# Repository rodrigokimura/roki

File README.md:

# RoKi

> An ergonomic, wireless, split mechanical keyboard — hardware, firmware and tooling in one repo.

**RoKi** (from the author's surname) is a custom, from-scratch split keyboard project. It covers the full stack: PCB design, 3D-printable case parts, CircuitPython firmware running on the [nice!nano v2](https://nicekeyboards.com/docs/nice-nano/) (wireless Bluetooth Low Energy controller), and a companion Python CLI / web UI / TUI to flash, configure and debug the board.

> ⚠️ **Status:** Work in progress. Breaking changes are expected.

---

## Features

- **Split layout** with BLE-based inter-half communication (no TRRS cable).
- **5 rows × 6 columns** per half, diode matrix.
- **Thumb cluster with analog thumbstick** (for pointer / scroll / layer control).
- **Rotary encoder** on each half.
- **Piezo buzzer** for audio feedback.
- **Layer system** with custom `layer_handler` (tap / hold / toggle commands).
- **HID support** for keyboard, mouse and consumer-control (media) keys, via `adafruit_hid`.
- **Per-side configuration** (primary / secondary) selected via environment.
- **Runtime calibration** of the analog thumbstick (deadzone, center, range).
- **Read-only filesystem toggle** at boot, driven by a hardware switch, so you can
  hot-swap between "keyboard mode" and "developer mode" without rebuilding firmware.

---

## Repository layout

```
roki/
├── roki/                    # Python package
│   ├── firmware/            # CircuitPython firmware (runs on nice!nano v2)
│   │   ├── boot.py          # Early boot: filesystem readonly switch
│   │   ├── code.py          # Main entry point, pin mapping
│   │   ├── kb.py            # Primary / Secondary keyboard classes
│   │   ├── keys.py          # HID key definitions and handlers
│   │   ├── layer_handler.py # Layer / Command system
│   │   ├── calibration.py   # Thumbstick calibration
│   │   ├── config.py        # Runtime config model + JSON loader
│   │   ├── service.py       # BLE service for half-to-half comms
│   │   ├── buzzer.py        # Audio feedback
│   │   ├── logging.py       # Color-coded adafruit_logging formatter
│   │   ├── params.py        # Env-based parameter singleton
│   │   └── config.json      # Default key map / layers
│   ├── cli/                 # Host-side CLI (typer)
│   │   ├── app.py           # `roki` command entry point
│   │   ├── utils.py         # Mount / unmount / lib install helpers
│   │   ├── file_management.py
│   │   ├── html_generator.py
│   │   └── logging.py
│   ├── tui/                 # Textual-based TUI key-map configurator
│   │   ├── app.py
│   │   ├── screens/
│   │   └── widgets/
│   └── templates/           # HTML templates for the web UI
├── tests/                   # pytest suite (firmware + cli)
├── kicad/roki/              # PCB design (schematic, layout, 3D step)
├── freecad/                 # Case, keycaps, thumbstick, encoder, etc.
├── conftest.py              # Global mocks for CircuitPython modules
└── pyproject.toml
```

---

## Hardware

| Item                | Choice                                        |
|---------------------|-----------------------------------------------|
| Microcontroller     | [nice!nano v2](https://nicekeyboards.com/docs/nice-nano/pinout-schematic/) (nRF52840, BLE) |
| Layout              | Split, 5×6 + thumb cluster + encoder per half |
| Switches            | MX-compatible, hotswap                        |
| Inter-half comms    | Bluetooth Low Energy (custom GATT service)    |
| Power               | Li-Po, per-half power switch                  |
| Analog input        | Thumbstick (X / Y + push)                     |

PCB sources live in [`kicad/roki/`](./kicad/roki/). Case, keycaps and mechanical parts live in [`freecad/`](./freecad/) as `.FCStd` files.

---

## Firmware (CircuitPython)

Runs on CircuitPython for nRF52840. The firmware is structured around a `Primary` / `Secondary` pair of keyboard halves:

- **Primary** holds the full config, scans its own matrix, talks HID over BLE to the host, and receives key events from the secondary over a custom BLE service.
- **Secondary** scans its matrix and forwards events to the primary.

The side is chosen at boot via the `IS_LEFT_SIDE` environment variable (or the `boot.py` switch pin), so the same code runs on both halves.

### Pin mapping

Defined in [`roki/firmware/code.py`](./roki/firmware/code.py):

```python
Roki(
    row_pins=("P0_24", "P1_00", "P0_11", "P1_04", "P1_06"),
    column_pins=("P0_09", "P0_10", "P1_11", "P1_13", "P1_15", "P0_02"),
    buzzer_pin="P0_06",
    thumb_stick_pins=("P0_22", "AIN7", "AIN5"),  # switch, X, Y
    encoder_pins=("P0_17", "P0_20"),
)
```

See the [nice!nano pinout & schematic](https://nicekeyboards.com/docs/nice-nano/pinout-schematic/) for reference.

### Boot-time write protection

`boot.py` reads pin `P0_22` on startup. When the switch is **open** the filesystem is mounted read-only (normal keyboard mode); when **closed**, read-write — useful for editing files over USB without your OS fighting CircuitPython.

---

## Host-side tooling

A `typer` CLI is installed as `roki`:

```sh
roki upload        # (alias: u)  Flash firmware + libs to the connected board
roki run           #             Launch the TUI key-map configurator
roki serve         #             Start the FastAPI + Jinja web config UI
roki generate      # (alias: g)  Generate static HTML / artifacts
roki config        #             Show / edit config.json
```

### Install

```sh
uv sync
```

(Uses [uv](https://docs.astral.sh/uv/) as the package manager; Python 3.12+.)

### Run the tests

```sh
uv run pytest
```

With coverage:

```sh
uv run pytest --cov=roki --cov-report=term
```

Current coverage: **88%** across ~2.3k lines of source with 109 tests.

### Run the web configurator locally (HTTPS)

```sh
# Generate self-signed certs once
openssl req -x509 -newkey rsa:2048 -keyout key.pem -out cert.pem -days 365

uv run roki serve
```

---

## Environment variables

Set in `roki/firmware/settings.toml` on the board, or via your shell for host-side runs:

| Variable        | Default | Meaning                                     |
|-----------------|---------|---------------------------------------------|
| `IS_LEFT_SIDE`  | `1`     | `1` for primary (left), `0` for secondary   |
| `DEBUG`         | `0`     | `1` enables the stream logger               |
| `LOG_LEVEL`     | `0`     | Standard logging levels (10 = DEBUG, etc.)  |

---

## Development workflow

This repo uses [commitizen](https://commitizen-tools.github.io/commitizen/) for [Conventional Commits](https://www.conventionalcommits.org/) and [ruff](https://docs.astral.sh/ruff/) for linting / import sorting.

```sh
uv run cz commit            # interactive commit
uv run ruff check --fix .   # lint + autofix
uv run ruff format .        # format
```

Pre-commit hooks are configured in [`.pre-commit-config.yaml`](./.pre-commit-config.yaml).

---

## License

[MIT](./LICENSE) © Rodrigo Eiti Kimura

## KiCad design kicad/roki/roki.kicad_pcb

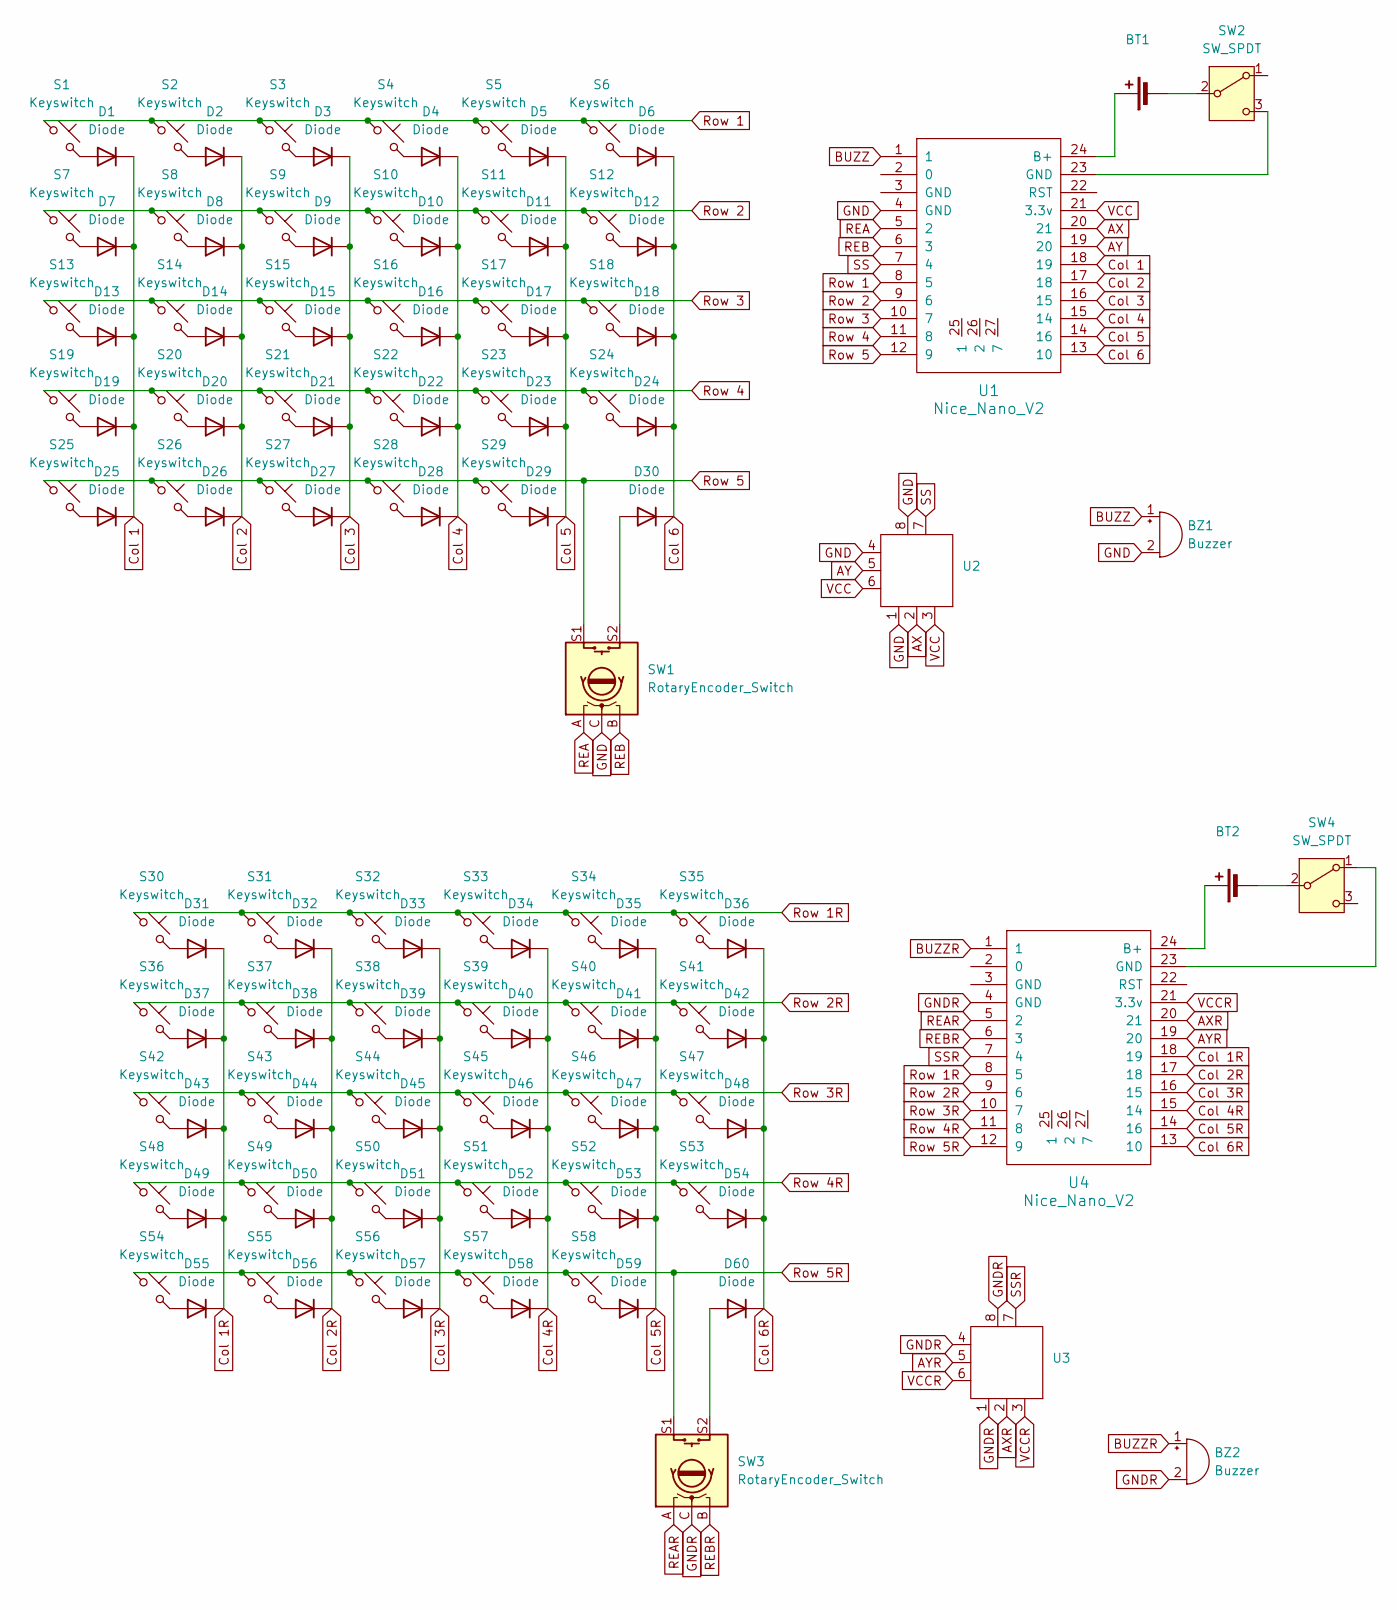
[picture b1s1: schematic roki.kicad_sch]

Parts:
BT1, BT2: Battery_Cell; BatteryHolder_MPD_BH-18650-PC2
BZ1, BZ2: Buzzer; Buzzer_TDK_PS1240P02BT_D12.2mm_H6.5mm
D1, D2, D3, D4, D5, D6, D7, D8, D9, D10, D11, D12, D13, D14, D15, D16, D17, D18, D19, D20, D21, D22, D23, D24, D25, D26, D27, D28, D29, D30, D31, D32, D33, D34, D35, D36, D37, D38, D39, D40, D41, D42, D43, D44, D45, D46, D47, D48, D49, D50, D51, D52, D53, D54, D55, D56, D57, D58, D59, D60: Diode; Diode_SOD-123
S1, S2, S3, S4, S5, S6, S7, S8, S9, S10, S11, S12, S13, S14, S15, S16, S17, S18, S19, S20, S21, S22, S23, S24, S25, S26, S27, S28, S29, S30, S31, S32, S33, S34, S35, S36, S37, S38, S39, S40, S41, S42, S43, S44, S45, S46, S47, S48, S49, S50, S51, S52, S53, S54, S55, S56, S57, S58: Keyswitch; Hotswap_MX_1.00u
SW1, SW3: RotaryEncoder_Switch; RotaryEncoder_Alps_EC11E-Switch_Vertical_H20mm
SW2, SW4: SW_SPDT; SW_SPDT_PCM12
U1, U4: Nice_Nano_V2
U2, U3: thumb_stick

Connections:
AX: U1.20 (21), U2.2
AXR: U3.2, U4.20 (21)
AY: U1.19 (20), U2.5
AYR: U3.5, U4.19 (20)
BUZZ: BZ1.1 (+), U1.1
BUZZR: BZ2.1 (+), U4.1
Col 1: D1.1 (K), D7.1 (K), D13.1 (K), D19.1 (K), D25.1 (K), U1.18 (19)
Col 1R: D31.1 (K), D37.1 (K), D43.1 (K), D49.1 (K), D55.1 (K), U4.18 (19)
Col 2: D2.1 (K), D8.1 (K), D14.1 (K), D20.1 (K), D26.1 (K), U1.17 (18)
Col 2R: D32.1 (K), D38.1 (K), D44.1 (K), D50.1 (K), D56.1 (K), U4.17 (18)
Col 3: D3.1 (K), D9.1 (K), D15.1 (K), D21.1 (K), D27.1 (K), U1.16 (15)
Col 3R: D33.1 (K), D39.1 (K), D45.1 (K), D51.1 (K), D57.1 (K), U4.16 (15)
Col 4: D4.1 (K), D10.1 (K), D16.1 (K), D22.1 (K), D28.1 (K), U1.15 (14)
Col 4R: D34.1 (K), D40.1 (K), D46.1 (K), D52.1 (K), D58.1 (K), U4.15 (14)
Col 5: D5.1 (K), D11.1 (K), D17.1 (K), D23.1 (K), D29.1 (K), U1.14 (16)
Col 5R: D35.1 (K), D41.1 (K), D47.1 (K), D53.1 (K), D59.1 (K), U4.14 (16)
Col 6: D6.1 (K), D12.1 (K), D18.1 (K), D24.1 (K), D30.1 (K), U1.13 (10)
Col 6R: D36.1 (K), D42.1 (K), D48.1 (K), D54.1 (K), D60.1 (K), U4.13 (10)
GND: BZ1.2 (-), SW1.C, U1.4 (GND), U2.1, U2.4, U2.8
GNDR: BZ2.2 (-), SW3.C, U3.1, U3.4, U3.8, U4.4 (GND)
unnamed: BT1.1 (+), U1.24 (B+)
unnamed: BT1.2 (-), SW2.2 (B)
unnamed: BT2.1 (+), U4.24 (B+)
unnamed: BT2.2 (-), SW4.2 (B)
unnamed: D1.2 (A), S1.2
unnamed: D2.2 (A), S2.2
unnamed: D3.2 (A), S3.2
unnamed: D4.2 (A), S4.2
unnamed: D5.2 (A), S5.2
unnamed: D6.2 (A), S6.2
unnamed: D7.2 (A), S7.2
unnamed: D8.2 (A), S8.2
unnamed: D9.2 (A), S9.2
unnamed: D10.2 (A), S10.2
unnamed: D11.2 (A), S11.2
unnamed: D12.2 (A), S12.2
unnamed: D13.2 (A), S13.2
unnamed: D14.2 (A), S14.2
unnamed: D15.2 (A), S15.2
unnamed: D16.2 (A), S16.2
unnamed: D17.2 (A), S17.2
unnamed: D18.2 (A), S18.2
unnamed: D19.2 (A), S19.2
unnamed: D20.2 (A), S20.2
unnamed: D21.2 (A), S21.2
unnamed: D22.2 (A), S22.2
unnamed: D23.2 (A), S23.2
unnamed: D24.2 (A), S24.2
unnamed: D25.2 (A), S25.2
unnamed: D26.2 (A), S26.2
unnamed: D27.2 (A), S27.2
unnamed: D28.2 (A), S28.2
unnamed: D29.2 (A), S29.2
unnamed: D30.2 (A), SW1.S2
unnamed: D31.2 (A), S30.2
unnamed: D32.2 (A), S31.2
unnamed: D33.2 (A), S32.2
unnamed: D34.2 (A), S33.2
unnamed: D35.2 (A), S34.2
unnamed: D36.2 (A), S35.2
unnamed: D37.2 (A), S36.2
unnamed: D38.2 (A), S37.2
unnamed: D39.2 (A), S38.2
unnamed: D40.2 (A), S39.2
unnamed: D41.2 (A), S40.2
unnamed: D42.2 (A), S41.2
unnamed: D43.2 (A), S42.2
unnamed: D44.2 (A), S43.2
unnamed: D45.2 (A), S44.2
unnamed: D46.2 (A), S45.2
unnamed: D47.2 (A), S46.2
unnamed: D48.2 (A), S47.2
unnamed: D49.2 (A), S48.2
unnamed: D50.2 (A), S49.2
unnamed: D51.2 (A), S50.2
unnamed: D52.2 (A), S51.2
unnamed: D53.2 (A), S52.2
unnamed: D54.2 (A), S53.2
unnamed: D55.2 (A), S54.2
unnamed: D56.2 (A), S55.2
unnamed: D57.2 (A), S56.2
unnamed: D58.2 (A), S57.2
unnamed: D59.2 (A), S58.2
unnamed: D60.2 (A), SW3.S2
unnamed: SW2.3 (C), U1.23 (GND)
unnamed: SW4.1 (A), U4.23 (GND)
REA: SW1.A, U1.5 (2)
REAR: SW3.A, U4.5 (2)
REB: SW1.B, U1.6 (3)
REBR: SW3.B, U4.6 (3)
Row 1: S1.1, S2.1, S3.1, S4.1, S5.1, S6.1, U1.8 (5)
Row 1R: S30.1, S31.1, S32.1, S33.1, S34.1, S35.1, U4.8 (5)
Row 2: S7.1, S8.1, S9.1, S10.1, S11.1, S12.1, U1.9 (6)
Row 2R: S36.1, S37.1, S38.1, S39.1, S40.1, S41.1, U4.9 (6)
Row 3: S13.1, S14.1, S15.1, S16.1, S17.1, S18.1, U1.10 (7)
Row 3R: S42.1, S43.1, S44.1, S45.1, S46.1, S47.1, U4.10 (7)
Row 4: S19.1, S20.1, S21.1, S22.1, S23.1, S24.1, U1.11 (8)
Row 4R: S48.1, S49.1, S50.1, S51.1, S52.1, S53.1, U4.11 (8)
Row 5: S25.1, S26.1, S27.1, S28.1, S29.1, SW1.S1, U1.12 (9)
Row 5R: S54.1, S55.1, S56.1, S57.1, S58.1, SW3.S1, U4.12 (9)
SS: U1.7 (4), U2.7
SSR: U3.7, U4.7 (4)
VCC: U1.21 (3.3v), U2.3, U2.6
VCCR: U3.3, U3.6, U4.21 (3.3v)

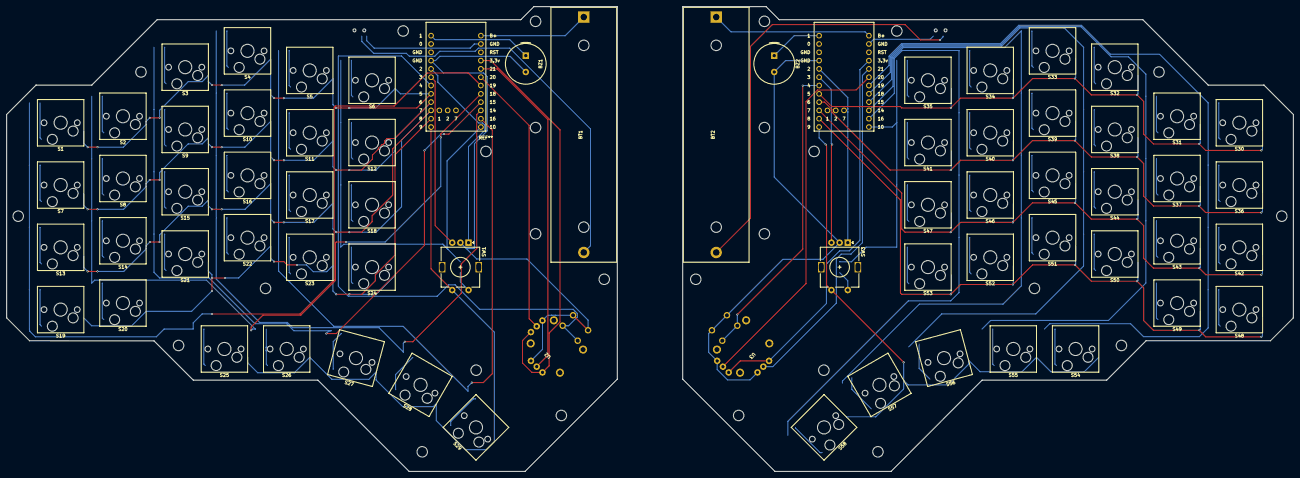
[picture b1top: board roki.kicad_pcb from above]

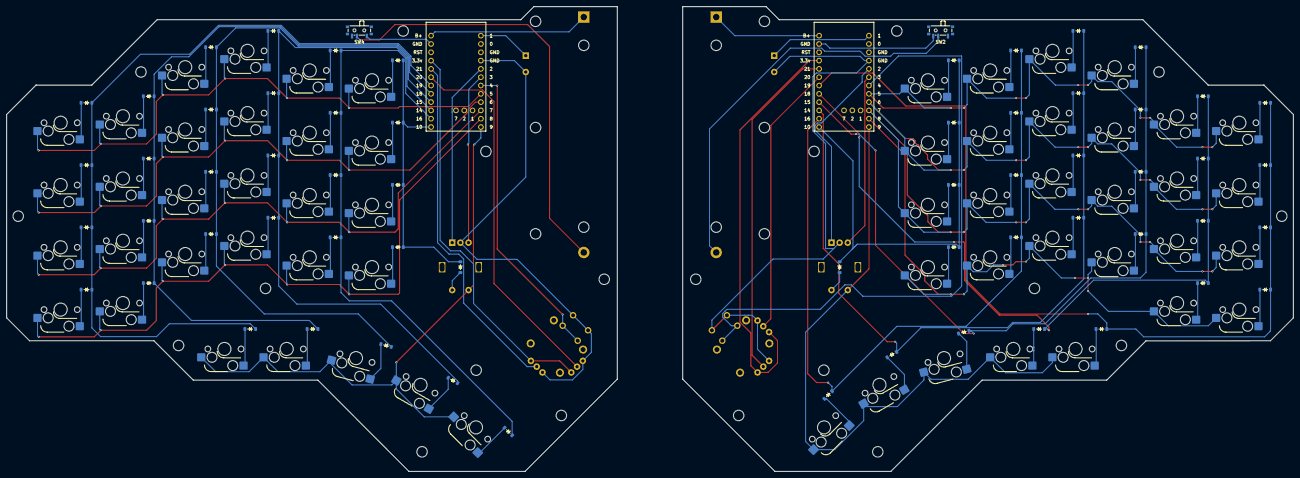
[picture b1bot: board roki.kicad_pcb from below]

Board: 2 copper layers, 393.6 x 142.2 mm, 130 parts (62 on the bottom side), 104 nets.

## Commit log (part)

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2024-09-05 feat: create first working version
2024-09-05 build(deps): update deps
2024-09-12 feat: add file management functions
2024-09-12 refactor(cli): abstract low-level file management logic
2024-09-12 refactor(firmware): remove unused code
2024-09-12 ci: add and configure commitizen
2024-09-12 feat(firmware): use scroll lock as layer state
2024-09-12 fix(firmware): protect against exception
2024-09-17 feat(firmware): add first draft of central-peripheral communication
2024-09-18 feat(firmware): implement packet buffer service
2024-09-18 fix(firmware): reimplement layers using central-peripheral connection
2024-10-09 fix(cli): copy file after its update
2024-10-29 perf(firmware): decrease connection interval
2024-11-05 feat(firmware): add encoder object
2024-11-05 feat(firmware): add main class for the keyboard
2024-11-05 refactor(firmware): use main class
2024-11-05 perf(firmware): cache row and column count
2024-11-09 feat(firmware): add encoder feature
2024-11-09 docs(readme): add pinout and schematic link
2024-11-09 refactor(firmware): simplify methods
2024-11-29 feat(cli): add commands for configuration page
2024-12-02 build(deps): add textual
2024-12-02 fix: remove unused code
2024-12-02 feat(tui): add configurator tui
2024-12-08 feat(firmware): implement new communication protocol
2024-12-08 fix(cli): change options for upload command
2024-12-09 build(poetry): add coverage deps
2024-12-10 feat(firmware): add thumb stick analog inputs
2024-12-10 test: add tests
2024-12-10 feat(firmware): add protocol to send and parse thumb stick data
2024-12-11 fix(tui): fix imports
2024-12-12 feat(firmware): process secondary thumb stick
2024-12-15 feat(kicad): add kicak files
2024-12-15 feat(freecad): add freecad files
2024-12-24 build(deps): bump jinja2 from 3.1.4 to 3.1.5
    Bumps [jinja2](https://github.com/pallets/jinja) from 3.1.4 to 3.1.5.
    - [Release notes](https://github.com/pallets/jinja/releases)
    - [Changelog](https://github.com/pallets/jinja/blob/main/CHANGES.rst)
    - [Commits](https://github.com/pallets/jinja/compare/3.1.4...3.1.5)
    ---
    updated-dependencies:
2024-12-25 feat(firmware): add calibration algorithm
2025-01-08 feat(cli): allow https on local setup
2025-01-09 build(deps): fix dependency tree
2025-01-09 fix(kicad): fix thumb stick pin schematics
2025-01-23 feat(firmware): write calibration data
2025-01-24 feat(firmware): implement thumb stick mid value
2025-01-24 feat(firmware): implement float to byte conversion
2025-01-28 feat(firmware): add message constants
2025-01-29 ci(pre-commit): update config
2025-01-29 feat(cli): improve upload command to keep calibration config
2025-01-29 feat(cli): ignore cache files when uploading
2025-01-29 feat(cli): add more valid options for side identification
2025-01-30 test(firmware): add test to check instantiation of the main classes
2025-01-31 test: improve test coverage
2025-01-31 Create LICENSE
2025-01-31 docs: add license
2025-02-01 test: increase coverage
2025-02-01 test: add missing tests
2025-02-02 test: add tests for layer handler
2025-02-02 test: add tests for cli utils
2025-02-03 fix(firmware): postpone import
2025-02-03 fix(firmware): add null check
2025-02-03 fix(firmware): fix indexes
2025-02-04 test: add missing test cases
2025-02-11 feat(kicad): add right side
2025-03-13 feat(firmware): add display code (WIP)
2025-03-13 feat(tui): add search input
2025-03-14 refactor(firmware): remove asyncio
2025-03-15 feat(firmware): add buzzer class
2025-03-15 feat(firmware): add notification sounds
2025-03-18 feat(kicad): update pcb
2025-03-19 feat(kicad): pin components
2025-03-25 feat(kicad): update files
2025-05-20 feat(freecad): create main model
2025-06-29 build(uv): change to uv
2025-06-29 build(uv): move deps to dev group
2025-06-29 build(uv): sync lock file
2025-06-29 build(uv): move deps
2025-06-29 feat(cli): postpone imports
2025-06-29 feat(freecad): update models
2025-06-29 feat(cli): add condition for minify
2025-06-29 fix(firmware): use same config instance
2025-11-16 feat(freecad): udpate models
2025-12-02 Add keycap model
2026-02-01 feat(cli): allow command to run on windows
2026-02-04 feat(firmware): implement logging
2026-02-06 feat(cli): inject cli parameters to code to run using mcu
2026-02-09 build(uv): add ty for type checking
2026-02-09 refactor(firmware): make implementation pass type checking
2026-02-21 build(uv): update deps
2026-02-21 feat(firmware): implement weighted loop
2026-02-24 perf(firmware): improve performance on key matrix fetching
2026-02-24 test(firmware): fix keywrapper test
2026-03-17 perf(firmware): assign different actions in initialization time
2026-03-19 feat(firmware): release kb key on layer handler key press
2026-03-26 fix(firmware): fix key order when reading on secondary side
2026-04-24 Update KiCad PCB, FreeCAD models, and CLI app
2026-04-24 feat(firmware): change default value for extras
2026-04-25 test: add tests for boot, cli logging and firmware logging
    - rewrite tests/firmware/test_boot.py to cover Params.from_env,
    switch pin configuration, read-only vs read-write remount,
    RuntimeError handling and switch deinit (8 tests)
    - add tests/cli/test_logging.py covering format_by_level,
    LevelBasedFormatter and configure_logging (11 tests)
    - add tests/firmware/test_logging.py covering format_by_level,
2026-04-25 style: organize imports with ruff
    Applied `ruff check --select I --fix .` across the codebase, sorting
    and grouping imports in 12 Python files (4 under `roki/` and 8 under
    `tests/`). No behavioral changes; all 109 tests still pass.
2026-04-25 style: organize imports with ruff (#69)
    Applied `ruff check --select I --fix .` across the codebase, sorting
    and grouping imports in 12 Python files (4 under `roki/` and 8 under
    `tests/`). No behavioral changes; all 109 tests still pass.
2026-04-25 docs: rewrite README with full project description
    Expand the README from a near-empty stub into a proper project overview
    covering:
    - what RoKi is (split BLE keyboard, full-stack project)
    - feature list
    - repository layout
    - hardware summary
2026-04-25 docs: rewrite README with full project description (#70)
    Expand the README from a near-empty stub into a proper project overview
    covering:
    - what RoKi is (split BLE keyboard, full-stack project)
    - feature list
    - repository layout
    - hardware summary
2026-05-18 docs: add rust + embassy port plan
    Add comprehensive migration plan for rewriting the CircuitPython
    firmware in Rust with the Embassy async framework. Covers crate
    selection, module mapping, task architecture, pin mapping,
    incremental milestones, and open questions.
2026-05-19 feat(rust-firmware): make roki-firmware-rs compile
    - Align all hardware APIs to embassy-nrf v0.2.0:
    - SimplePwm::new_1ch, set_period for buzzer
    - Qdec::new with Irqs binding, SamplePeriod syntax
    - Saadc::new with concrete pins, ChannelConfig fields
    - Matrix::new with concrete pins + AnyPin rows
    - Add embedded-storage dependency for Nvmc NorFlash trait
2026-05-19 chore(rust-firmware): clean compiler warnings and add left-side feature flag
    - Remove unused imports across modules (keymap, layers, matrix, primary, config, ble/hid_service, ble/roki_service)
    - Rename unused variables with prefix (buzzer tone duration)
    - Mark unused calibration.limit as _limit
    - Remove unused RawConfig struct
    - Add [features] left-side = [] in Cargo.toml to suppress unexpected_cfgs
    - Remove duplicate Timer import in main.rs
2026-05-19 fix(rust-firmware): enable embassy integrated-timers feature
    Cargo.toml: Add to features.
    This links the FFI symbol so
    cargo build completes instead of failing with undefined reference
    at link time. The already provides
    the concrete time driver; executor just needed the glue feature.
    Milestone: passes cleanly on thumbv7em-none-eabihf.
2026-05-19 docs(plan): update RUST_EMBASSY_PORT_PLAN with milestones M0-M2 status
2026-05-19 feat(keymap): add full keypad + application keycodes
    Add KeypadNumlock through KeypadPeriod (0x53–0x63) and Application
    (0x65) to the Keycode enum, with matching from_str() arms so users
    can assign numpad keys in config.json. All 85 keys in the current
    config.json remain covered; this extends support for future layouts.
2026-05-19 build(uf2): add Makefile, build-uf2.sh, and README
    - build-uf2.sh: one-shot release build + elf2uf2-rs conversion
    - Makefile: convenient targets (build, release, uf2, check, clean)
    - README.md: build instructions, architecture overview, milestone tracker
    Milestone: UF2 build workflow complete.
2026-05-19 docs(plan): mark UF2 build and boot calibration complete
2026-05-19 feat(ble): wire SoftDevice, RokiService GATT, inter-half scan/connect
    - ble/mod.rs: init_softdevice() with nRF52840 RC osc + single-conn config
    - ble/roki_service.rs:
    - RokiServer: ServiceBuilder registration, notify_value() on char handle
    - RokiClient: gatt_client::Client impl, CCCD enable, HVX dispatch
    - Export ROKI_UUID_128 bytes for advertisement matching
    - side/secondary.rs:
2026-05-19 docs(plan): mark M3–M4 BLE inter-half complete
2026-05-19 feat(hogp): M5 — HID over GATT (HOGP) service for host OS
    - ble/hid_service.rs: Register HID Service (0x1812) with full GATT server:
    - HID Information, Report Map (keyboard+mouse+consumer), Protocol Mode,
    HID Control Point, 3× Input Report characteristics (keyboard, mouse,
    consumer), each with Report Reference descriptor (0x2908).
    - send_keyboard(), send_mouse(), send_consumer() via notify_value().
    - ble/mod.rs: conn_count=2, hvn_tx_queue_size=8 for dual-role primary.
2026-05-19 polish: zero warnings, consumer HOGP reports, log clarity
    - config.rs: #[allow(dead_code)] on serde serialize stubs (never invoked)
    - thumbstick.rs: remove unused on shadowed calibration variable
    - keymap.rs: add HidState::consumer_report() for media-key dispatch
    - side/primary.rs:
    - Wire consumer/media HID reports into main loop (change-detected)
    - Restore mouse report dispatch (was accidentally dropped in prior edit)
2026-05-19 feat(reconnect): auto-reconnect loops for host + secondary on both halves
    - side/primary.rs: Split into background link tasks (secondary_link_task,
    host_link_task) and main HID loop. Both links auto-retry on disconnect:
    secondary_link_task: scan→connect→discover→enable_notifs→gatt_client::run,
    loops forever with 1s backoff on any failure.
    host_link_task: advertise_connectable→accept host→store in HOST_CONN,
    loops forever with 5s backoff on failure.
2026-05-19 docs(plan): mark reconnection milestone complete
2026-05-19 docs: comprehensive on-device testing guide
    - Add hardware requirements, debug probe pinout
    - Add step-by-step test checklist: matrix, encoder, thumbstick, HID host,
    BLE pairing, reconnection resilience, boot-time calibration, power
    - Add quick-reference one-liners for right/left build, RTT logs, trace mode
    - Update milestone tracker to reflect completion status
2026-05-19 docs: document M9 USB MSC drag-and-drop keymap as future milestone
    - README.md:
    - Add section 8: compile-time keymap change workflow
    - Add Future milestones section with M7–M9
    - Add detailed M9 plan: USB MSC over embassy-usb, virtual FAT,
    SCSI write detection, JSON validation, flash-backed storage,
    CRC-32 safety, VBUS-only activation
